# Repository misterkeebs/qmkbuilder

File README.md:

# Keyboard Firmware Builder

## Setup

To set up the project for development, run `npm install` in the root of the project to install dependencies.

Create a `local.json` file in `src/const`, in the format:

    {
		"API": "URL to server /build route",
		"PRESETS": "URL to static/presets folder"
	}

## Compiling

To compile, run `npm run build`.

## Deploying

To deploy a production version of the application, run `npm run deploy`.

## License

Keyboard Firmware Builder is under the GNU GPL v3 license. The license information for QMK Firmware can be found at https://qmk.fm/license/.

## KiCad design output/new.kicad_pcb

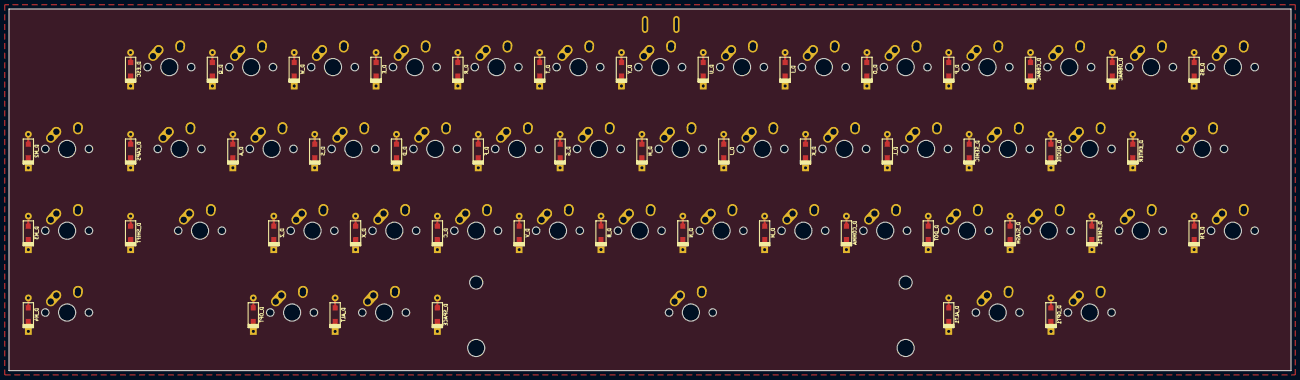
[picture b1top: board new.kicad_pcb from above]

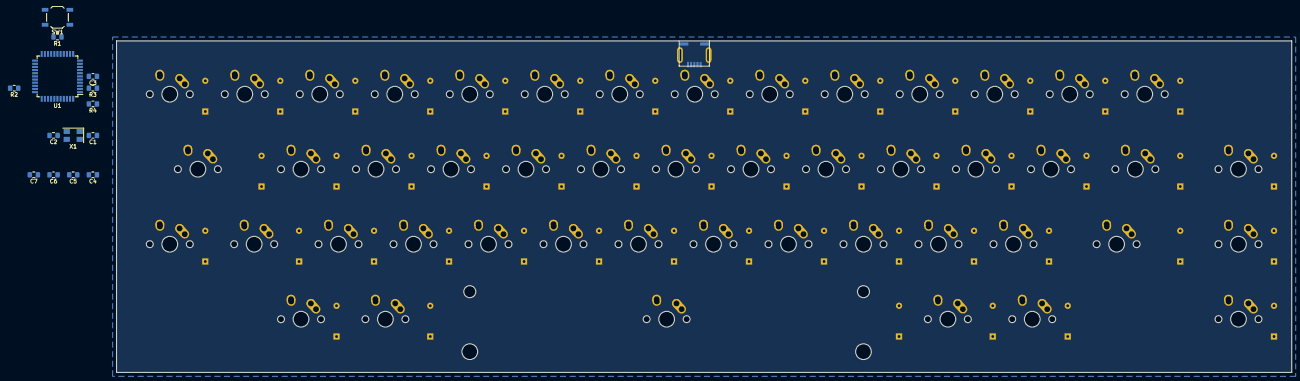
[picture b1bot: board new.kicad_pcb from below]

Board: 2 copper layers, 298.5 x 84.2 mm, 111 parts (15 on the bottom side), 74 nets, no tracks yet.

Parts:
C1, C2, C3, C4, C5, C6, C7: 22pF; C_0805_2012Metric_Pad1.15x1.40mm_HandSolder
D_A: D; D_SOD123_axial
D_ALT, D_ALT1: D; D_SOD123_axial
D_B: D; D_SOD123_axial
D_BS: D; D_SOD123_axial
D_C: D; D_SOD123_axial
D_CAPS: D; D_SOD123_axial
D_CBRAC: D; D_SOD123_axial
D_COMMA: D; D_SOD123_axial
D_D: D; D_SOD123_axial
D_DOT: D; D_SOD123_axial
D_E: D; D_SOD123_axial
D_ENTER: D; D_SOD123_axial
D_ESC: D; D_SOD123_axial
D_F: D; D_SOD123_axial
D_FN: D; D_SOD123_axial
D_G: D; D_SOD123_axial
D_H: D; D_SOD123_axial
D_I: D; D_SOD123_axial
D_J: D; D_SOD123_axial
D_K: D; D_SOD123_axial
D_L: D; D_SOD123_axial
D_M, D_M2, D_M3, D_M4: D; D_SOD123_axial
D_N: D; D_SOD123_axial
D_O: D; D_SOD123_axial
D_OBRAC: D; D_SOD123_axial
D_OPT, D_OPT1: D; D_SOD123_axial
D_P: D; D_SOD123_axial
D_Q: D; D_SOD123_axial
D_QUOTE: D; D_SOD123_axial
D_R: D; D_SOD123_axial
D_S: D; D_SOD123_axial
D_SEMIC: D; D_SOD123_axial
D_SHIFT, D_SHIFT1: D; D_SOD123_axial
D_SLASH: D; D_SOD123_axial
D_SPACE: D; D_SOD123_axial
D_T: D; D_SOD123_axial
D_U: D; D_SOD123_axial
D_V: D; D_SOD123_axial
D_W: D; D_SOD123_axial
D_X: D; D_SOD123_axial
D_Y: D; D_SOD123_axial
D_Z: D; D_SOD123_axial
K_A: KEYSW; MX-1U-NoLED
K_ALT, K_ALT1: KEYSW; MX-1.25U-NoLED
K_B: KEYSW; MX-1U-NoLED
K_BS: KEYSW; MX-1U-NoLED
K_C: KEYSW; MX-1U-NoLED
K_CAPS: KEYSW; MX-1.25U-NoLED
K_CBRAC: KEYSW; MX-1U-NoLED
K_COMMA: KEYSW; MX-1U-NoLED
K_D: KEYSW; MX-1U-NoLED
K_DOT: KEYSW; MX-1U-NoLED
K_E: KEYSW; MX-1U-NoLED
K_ENTER: KEYSW; MX-1.75U-NoLED
K_ESC: KEYSW; MX-1U-NoLED
K_F: KEYSW; MX-1U-NoLED
K_FN: KEYSW; MX-1U-NoLED
K_G: KEYSW; MX-1U-NoLED
K_H: KEYSW; MX-1U-NoLED
K_I: KEYSW; MX-1U-NoLED
K_J: KEYSW; MX-1U-NoLED
K_K: KEYSW; MX-1U-NoLED
K_L: KEYSW; MX-1U-NoLED
K_M, K_M2, K_M3, K_M4: KEYSW; MX-1U-NoLED
K_N: KEYSW; MX-1U-NoLED
K_O: KEYSW; MX-1U-NoLED
K_OBRAC: KEYSW; MX-1U-NoLED
K_OPT, K_OPT1: KEYSW; MX-1U-NoLED
K_P: KEYSW; MX-1U-NoLED
K_Q: KEYSW; MX-1U-NoLED
K_QUOTE: KEYSW; MX-1U-NoLED
K_R: KEYSW; MX-1U-NoLED
K_S: KEYSW; MX-1U-NoLED
K_SEMIC: KEYSW; MX-1U-NoLED
K_SHIFT: KEYSW; MX-1.75U-NoLED
K_SHIFT1: KEYSW; MX-1.25U-NoLED
K_SLASH: KEYSW; MX-1U-NoLED
K_SPACE: KEYSW; MX-6.25U-NoLED
K_T: KEYSW; MX-1U-NoLED
K_U: KEYSW; MX-1U-NoLED
K_V: KEYSW; MX-1U-NoLED
K_W: KEYSW; MX-1U-NoLED
K_X: KEYSW; MX-1U-NoLED
K_Y: KEYSW; MX-1U-NoLED
K_Z: KEYSW; MX-1U-NoLED
R1, R2: 10k; R_0805_2012Metric_Pad1.15x1.40mm_HandSolder
R3, R4: 22u; R_0805_2012Metric_Pad1.15x1.40mm_HandSolder
SW1: SW_PUSH; SW_SPST_TL3342
U1: ATMEGA32U4; TQFP-44_10x10mm_P0.8mm
USB1: USB_mini_micro_B; USB_miniB_hirose_5S8
X1: XTAL_GND; Crystal_SMD_5032-4Pin_5.0x3.2mm

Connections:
/col0: D_M2.1, D_M3.1, D_M4.1, U1.28
/col1: D_CAPS.1, D_ESC.1, U1.29
/col2: D_Q.1, D_SHIFT.1, U1.30
/col3: D_A.1, D_OPT.1, D_W.1, D_Z.1, U1.12
/col4: D_ALT.1, D_E.1, D_S.1, D_X.1, U1.41
/col5: D_C.1, D_D.1, D_R.1, U1.40
/col6: D_F.1, D_T.1, D_V.1, U1.39
/col7: D_B.1, D_G.1, D_Y.1, U1.38
/col8: D_H.1, D_N.1, D_SPACE.1, D_U.1, U1.31
/col9: D_I.1, D_J.1, D_M.1, U1.32
/col10: D_COMMA.1, D_K.1, D_O.1, U1.18
/col11: D_ALT1.1, D_DOT.1, D_L.1, D_P.1, U1.19
/col12: D_CBRAC.1, D_SEMIC.1, D_SLASH.1, U1.20
/col13: D_OBRAC.1, D_OPT1.1, D_QUOTE.1, D_SHIFT1.1, U1.21
/col14: D_BS.1, D_ENTER.1, D_FN.1, U1.25
GND: C1.2, C2.2, C3.2, C4.2, C5.2, C6.2, C7.2, R2.2, SW1.1, U1.5, U1.15, U1.23, USB1.5, USB1.6, X1.3
unnamed: C1.1, U1.16, X1.1
unnamed: C2.1, U1.17, X1.2
unnamed: C3.1, U1.6
unnamed: D_A.2, K_A.2
unnamed: D_ALT1.2, K_ALT1.2
unnamed: D_ALT.2, K_ALT.2
unnamed: D_B.2, K_B.2
unnamed: D_BS.2, K_BS.2
unnamed: D_C.2, K_C.2
unnamed: D_CAPS.2, K_CAPS.2
unnamed: D_CBRAC.2, K_CBRAC.2
unnamed: D_COMMA.2, K_COMMA.2
unnamed: D_D.2, K_D.2
unnamed: D_DOT.2, K_DOT.2
unnamed: D_E.2, K_E.2
unnamed: D_ENTER.2, K_ENTER.2
unnamed: D_ESC.2, K_ESC.2
unnamed: D_F.2, K_F.2
unnamed: D_FN.2, K_FN.2
unnamed: D_G.2, K_G.2
unnamed: D_H.2, K_H.2
unnamed: D_I.2, K_I.2
unnamed: D_J.2, K_J.2
unnamed: D_K.2, K_K.2
unnamed: D_L.2, K_L.2
unnamed: D_M2.2, K_M2.2
unnamed: D_M3.2, K_M3.2
unnamed: D_M4.2, K_M4.2
unnamed: D_M.2, K_M.2
unnamed: D_N.2, K_N.2
unnamed: D_O.2, K_O.2
unnamed: D_OBRAC.2, K_OBRAC.2
unnamed: D_OPT1.2, K_OPT1.2
unnamed: D_OPT.2, K_OPT.2
unnamed: D_P.2, K_P.2
unnamed: D_Q.2, K_Q.2
unnamed: D_QUOTE.2, K_QUOTE.2
unnamed: D_R.2, K_R.2
unnamed: D_S.2, K_S.2
unnamed: D_SEMIC.2, K_SEMIC.2
unnamed: D_SHIFT1.2, K_SHIFT1.2
unnamed: D_SHIFT.2, K_SHIFT.2
unnamed: D_SLASH.2, K_SLASH.2
unnamed: D_SPACE.2, K_SPACE.2
unnamed: D_T.2, K_T.2
unnamed: D_U.2, K_U.2
unnamed: D_V.2, K_V.2
unnamed: D_W.2, K_W.2
unnamed: D_X.2, K_X.2
unnamed: D_Y.2, K_Y.2
unnamed: D_Z.2, K_Z.2
unnamed: R1.1, SW1.2, U1.13
unnamed: R2.1, U1.33
unnamed: R3.1, U1.3
unnamed: R4.1, U1.4
unnamed: R3.2, USB1.2
unnamed: R4.2, USB1.3
VCC: C4.1, C5.1, C6.1, C7.1, R1.2, U1.2, U1.14, U1.24, USB1.1

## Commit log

2019-03-14 initial KiCad PCB support
2019-03-14 feat: generates kicad zip file with footprints
2019-03-14 feat: first schematics implementation
2019-03-14 fix: project and pcb templates
2019-03-14 chore: added padding to the schematics output
2019-03-15 feat: schematics row wiring
2019-03-15 chore: removed output folder
2019-03-15 feat: schematics completed
2019-03-15 fix: key name and id
2019-03-15 feat: initial PCB generator
2019-03-15 feat: generate PCB component names
2019-03-15 feat: PCB keyboard layout
2019-03-15 feat: added planes and frames to the PCB
2019-03-15 feat: crystal and crystal caps
2019-03-15 feat: all components added to PCB
2019-03-15 feat: templates work on the browser
2019-03-15 feat: PCB generation finalized
2019-03-15 feat: added now support
2019-03-16 fix: better plane configurations
2019-03-16 feat: added microcontroller with row/col connections to schematics
2019-03-16 feat: added USB and USB connection resistors to schematics
2019-03-18 feat: VCC and microcontroller resistors/caps
2019-04-16 fix: connects the switch to its column
2019-04-16 feat: moved the diodes to the right side of key
2019-04-27 fix: diodes are on the row, not on the column net
2019-06-11 fix: crystal pinout
2019-06-11 feat: uses more accessible USB port footprint
2019-06-11 fix: 22R resistor label
2019-06-11 feat: added initial text to the PCB
2019-10-31 chore(deps): bump lodash from 4.17.11 to 4.17.15
    Bumps [lodash](https://github.com/lodash/lodash) from 4.17.11 to 4.17.15.
    - [Release notes](https://github.com/lodash/lodash/releases)
    - [Commits](https://github.com/lodash/lodash/compare/4.17.11...4.17.15)
2020-03-15 chore(deps): bump acorn from 5.7.3 to 5.7.4
    Bumps [acorn](https://github.com/acornjs/acorn) from 5.7.3 to 5.7.4.
    - [Release notes](https://github.com/acornjs/acorn/releases)
    - [Commits](https://github.com/acornjs/acorn/compare/5.7.3...5.7.4)
2020-07-17 chore(deps): bump lodash from 4.17.11 to 4.17.19
    Bumps [lodash](https://github.com/lodash/lodash) from 4.17.11 to 4.17.19.
    - [Release notes](https://github.com/lodash/lodash/releases)
    - [Commits](https://github.com/lodash/lodash/compare/4.17.11...4.17.19)
2020-07-30 chore(deps): bump elliptic from 6.4.1 to 6.5.3
    Bumps [elliptic](https://github.com/indutny/elliptic) from 6.4.1 to 6.5.3.
    - [Release notes](https://github.com/indutny/elliptic/releases)
    - [Commits](https://github.com/indutny/elliptic/compare/v6.4.1...v6.5.3)
2020-12-11 chore(deps): bump ini from 1.3.5 to 1.3.7
    Bumps [ini](https://github.com/isaacs/ini) from 1.3.5 to 1.3.7.
    - [Release notes](https://github.com/isaacs/ini/releases)
    - [Commits](https://github.com/isaacs/ini/compare/v1.3.5...v1.3.7)
2021-03-09 chore(deps): bump elliptic from 6.4.1 to 6.5.4
    Bumps [elliptic](https://github.com/indutny/elliptic) from 6.4.1 to 6.5.4.
    - [Release notes](https://github.com/indutny/elliptic/releases)
    - [Commits](https://github.com/indutny/elliptic/compare/v6.4.1...v6.5.4)
2021-05-07 chore(deps): bump ua-parser-js from 0.7.19 to 0.7.28
    Bumps [ua-parser-js](https://github.com/faisalman/ua-parser-js) from 0.7.19 to 0.7.28.
    - [Release notes](https://github.com/faisalman/ua-parser-js/releases)
    - [Commits](https://github.com/faisalman/ua-parser-js/compare/0.7.19...0.7.28)
2021-05-09 chore(deps): bump lodash from 4.17.11 to 4.17.21
    Bumps [lodash](https://github.com/lodash/lodash) from 4.17.11 to 4.17.21.
    - [Release notes](https://github.com/lodash/lodash/releases)
    - [Commits](https://github.com/lodash/lodash/compare/4.17.11...4.17.21)
2021-05-12 chore(deps): bump codemirror from 5.44.0 to 5.58.2
    Bumps [codemirror](https://github.com/codemirror/CodeMirror) from 5.44.0 to 5.58.2.
    - [Release notes](https://github.com/codemirror/CodeMirror/releases)
    - [Changelog](https://github.com/codemirror/CodeMirror/blob/master/CHANGELOG.md)
    - [Commits](https://github.com/codemirror/CodeMirror/compare/5.44.0...5.58.2)
2021-07-16 chore(deps): bump mixin-deep from 1.3.1 to 1.3.2
    Bumps [mixin-deep](https://github.com/jonschlinkert/mixin-deep) from 1.3.1 to 1.3.2.
    - [Release notes](https://github.com/jonschlinkert/mixin-deep/releases)
    - [Commits](https://github.com/jonschlinkert/mixin-deep/compare/1.3.1...1.3.2)
    ---
    updated-dependencies:
    - dependency-name: mixin-deep
2021-08-04 chore(deps): bump tar from 4.4.8 to 4.4.15
    Bumps [tar](https://github.com/npm/node-tar) from 4.4.8 to 4.4.15.
    - [Release notes](https://github.com/npm/node-tar/releases)
    - [Changelog](https://github.com/npm/node-tar/blob/main/CHANGELOG.md)
    - [Commits](https://github.com/npm/node-tar/compare/v4.4.8...v4.4.15)
    ---
    updated-dependencies:
2021-08-11 chore(deps): bump path-parse from 1.0.6 to 1.0.7
    Bumps [path-parse](https://github.com/jbgutierrez/path-parse) from 1.0.6 to 1.0.7.
    - [Release notes](https://github.com/jbgutierrez/path-parse/releases)
    - [Commits](https://github.com/jbgutierrez/path-parse/commits/v1.0.7)
    ---
    updated-dependencies:
    - dependency-name: path-parse
2021-09-01 chore(deps): bump tar from 4.4.8 to 4.4.19
    Bumps [tar](https://github.com/npm/node-tar) from 4.4.8 to 4.4.19.
    - [Release notes](https://github.com/npm/node-tar/releases)
    - [Changelog](https://github.com/npm/node-tar/blob/main/CHANGELOG.md)
    - [Commits](https://github.com/npm/node-tar/compare/v4.4.8...v4.4.19)
    ---
    updated-dependencies:
2022-01-27 chore(deps): bump cached-path-relative from 1.0.2 to 1.1.0
    Bumps [cached-path-relative](https://github.com/ashaffer/cached-path-relative) from 1.0.2 to 1.1.0.
    - [Release notes](https://github.com/ashaffer/cached-path-relative/releases)
    - [Commits](https://github.com/ashaffer/cached-path-relative/commits)
    ---
    updated-dependencies:
    - dependency-name: cached-path-relative
2022-02-11 chore(deps): bump pathval from 1.1.0 to 1.1.1
    Bumps [pathval](https://github.com/chaijs/pathval) from 1.1.0 to 1.1.1.
    - [Release notes](https://github.com/chaijs/pathval/releases)
    - [Changelog](https://github.com/chaijs/pathval/blob/master/CHANGELOG.md)
    - [Commits](https://github.com/chaijs/pathval/compare/v1.1.0...v1.1.1)
    ---
    updated-dependencies:
2022-06-22 chore(deps): bump shell-quote from 1.6.1 to 1.7.3
    Bumps [shell-quote](https://github.com/substack/node-shell-quote) from 1.6.1 to 1.7.3.
    - [Release notes](https://github.com/substack/node-shell-quote/releases)
    - [Changelog](https://github.com/substack/node-shell-quote/blob/master/CHANGELOG.md)
    - [Commits](https://github.com/substack/node-shell-quote/compare/1.6.1...1.7.3)
    ---
    updated-dependencies:
2022-12-03 chore(deps): bump decode-uri-component from 0.2.0 to 0.2.2
    Bumps [decode-uri-component](https://github.com/SamVerschueren/decode-uri-component) from 0.2.0 to 0.2.2.
    - [Release notes](https://github.com/SamVerschueren/decode-uri-component/releases)
    - [Commits](https://github.com/SamVerschueren/decode-uri-component/compare/v0.2.0...v0.2.2)
    ---
    updated-dependencies:
    - dependency-name: decode-uri-component
2022-12-10 chore(deps): bump express from 4.16.4 to 4.17.3
    Bumps [express](https://github.com/expressjs/express) from 4.16.4 to 4.17.3.
    - [Release notes](https://github.com/expressjs/express/releases)
    - [Changelog](https://github.com/expressjs/express/blob/master/History.md)
    - [Commits](https://github.com/expressjs/express/compare/4.16.4...4.17.3)
    ---
    updated-dependencies:
2022-12-23 add more presets
2022-12-23 Minor changes for new Bazel/Docker envrionments
    Removed extraneous files with spaces in names
    Changed server to serve static content
    Changed server to be configured with environment variables
    Changed server to handle SIGINT and SIGTERM
2022-12-23 Add license information
